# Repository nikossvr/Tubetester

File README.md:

# Tubetester
A dual psu regulated tube tester

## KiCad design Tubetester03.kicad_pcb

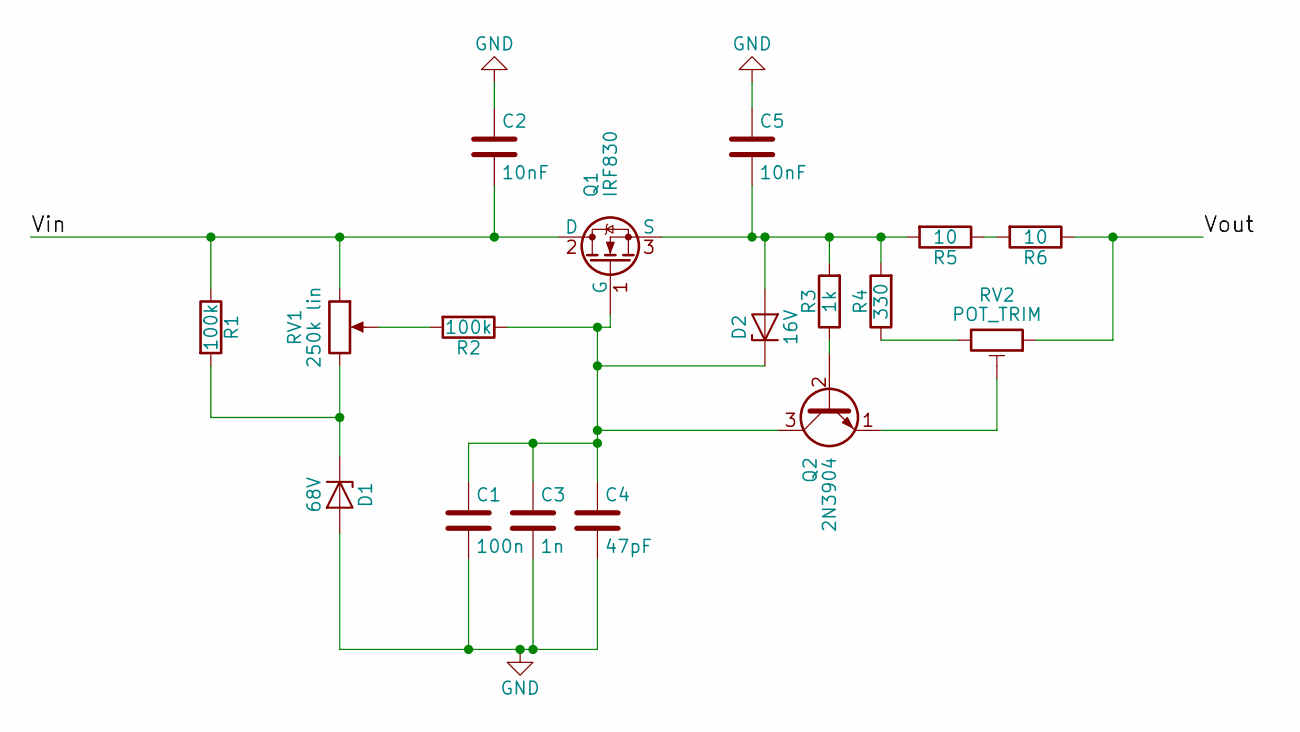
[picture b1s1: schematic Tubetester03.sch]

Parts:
C1: 100n; C_Rect_L16.5mm_W6.0mm_P15.00mm_MKT
C2, C5: 10nF; C_Rect_L11.5mm_W3.5mm_P10.00mm_MKT
C3: 1n; C_Rect_L7.2mm_W2.5mm_P5.00mm_FKS2_FKP2_MKS2_MKP2
C4: 47pF; C_Disc_D5.0mm_W2.5mm_P5.00mm
D1: 68V; D_A-405_P7.62mm_Horizontal
D2: 16V; D_A-405_P7.62mm_Horizontal
Q1: IRF830; TO-220-3_Vertical
Q2: 2N3904; TO-92_Molded_Narrow_Oval
R1: 100k; R_Axial_DIN0411_L9.9mm_D3.6mm_P12.70mm_Horizontal
R2: 100k; R_Axial_DIN0411_L9.9mm_D3.6mm_P5.08mm_Vertical
R3: 1k; R_Axial_DIN0411_L9.9mm_D3.6mm_P12.70mm_Horizontal
R4: 330; R_Axial_DIN0411_L9.9mm_D3.6mm_P12.70mm_Horizontal
R5, R6: 10; R_Axial_DIN0411_L9.9mm_D3.6mm_P12.70mm_Horizontal
RV1: 250k lin; Potentiometer_WirePads
RV2: POT_TRIM; Potentiometer_Trimmer_Bourns_3296Y

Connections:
/Vin: C2.2, Q1.2 (D), R1.1, RV1.1
/Vout: R6.1, RV2.1
GND: C1.2, C2.1, C3.2, C4.2, C5.1, D1.2 (A)
unnamed: C1.1, C3.1, C4.1, D2.1 (K), Q1.1 (G), Q2.3 (C), R2.1
unnamed: C5.2, D2.2 (A), Q1.3 (S), R3.2, R4.2, R5.2
unnamed: D1.1 (K), R1.2, RV1.3
unnamed: Q2.1 (E), RV2.2
unnamed: Q2.2 (B), R3.1
unnamed: R2.2, RV1.2
unnamed: R4.1, RV2.3
unnamed: R5.1, R6.2

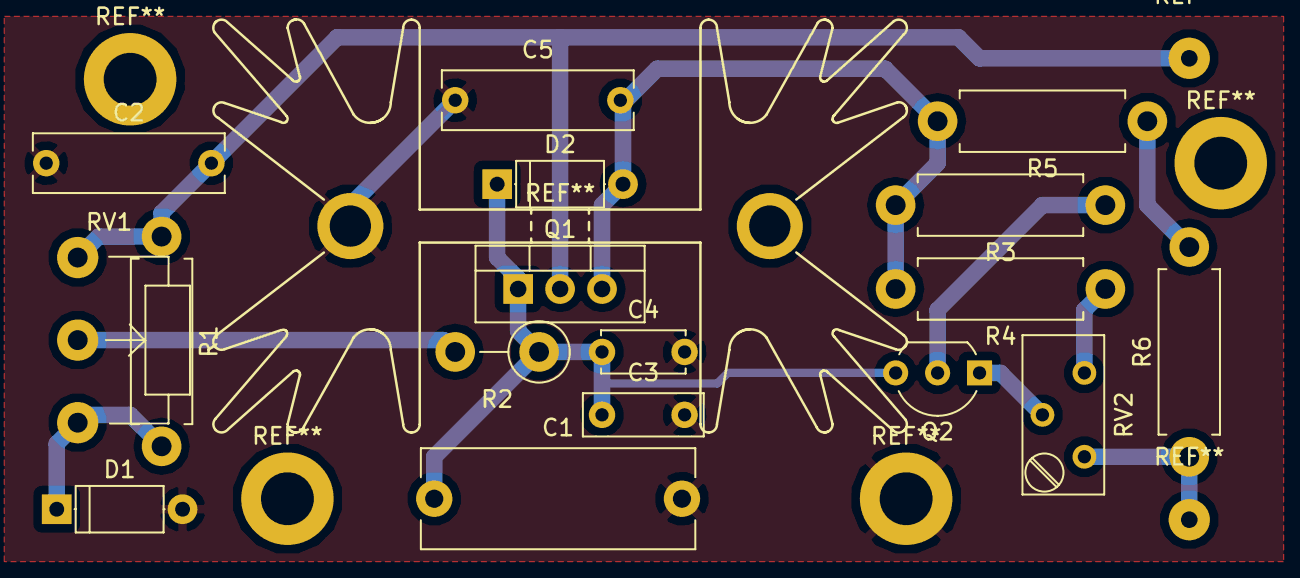
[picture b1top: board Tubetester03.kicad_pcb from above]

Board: 2 copper layers, 17 parts (0 on the bottom side), 11 nets.

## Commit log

2018-04-03 Rename Tubetester-cache.lib5 to Tubetester-cache.lib
